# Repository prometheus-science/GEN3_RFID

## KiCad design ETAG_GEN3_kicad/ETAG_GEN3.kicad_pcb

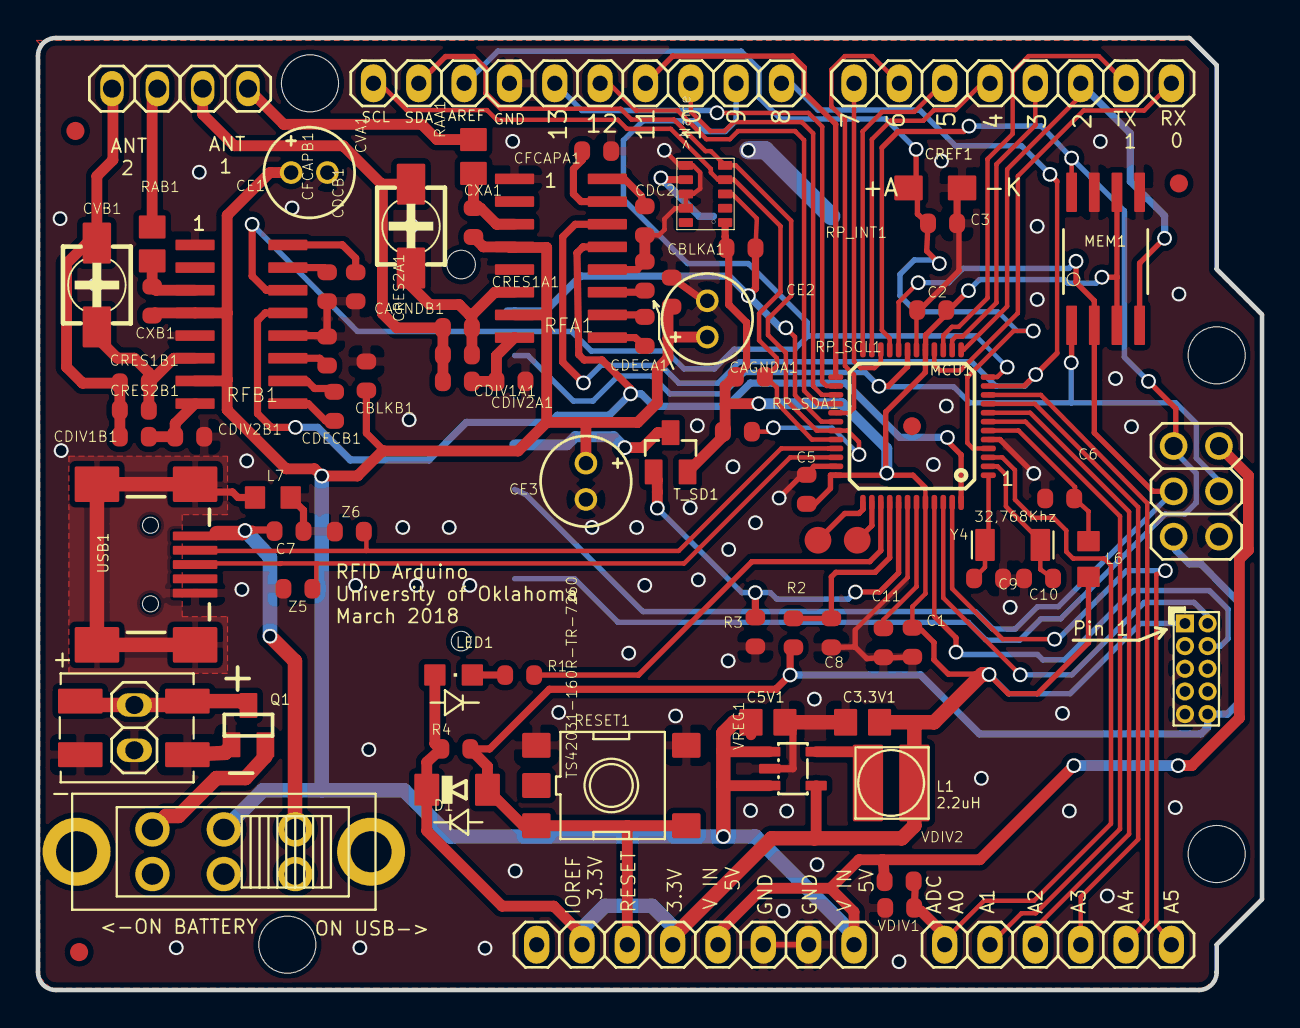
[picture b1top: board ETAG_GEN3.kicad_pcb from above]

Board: 2 copper layers, 68.6 x 53.3 mm, 89 parts (0 on the bottom side), 73 nets.

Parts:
@HOLE0, @HOLE1, @HOLE2, @HOLE3: (no value)
BAT1: 10MM_SM_COIN_CELL_CLIP
C1, C2, C3, C5, C6: 100nF; C0603-ROUND
C3.3V1, C5V1: 10uF; C0805
C7, C8: 10nF; C0603-ROUND
C9, C10: 22pF; C0603-ROUND
C11: 1uF; C0603-ROUND
CAGNDA1: 1uF; C0603-ROUND
CAGNDB1: 1uF; C0603-ROUND
CBLKA1: 100nF; C0603-ROUND
CBLKB1: 100nF; C0603-ROUND
CDC2: 10nF; C0603-ROUND
CDCB1: 10nF; C0603-ROUND
CDECA1: 100nF; C0603-ROUND
CDECB1: 100nF; C0603-ROUND
CDIV1A1, CDIV1B1: 22pF; C0603-ROUND
CDIV2A1, CDIV2B1: 1.5nF; C0603-ROUND
CE1, CE2, CE3: 150uF; E2-5
CFCAPA1: 10nF; C0603-ROUND
CFCAPB1: 10nF; C0603-ROUND
CON_P1: LITE_TRAP_2POS; LITE_TRAP_MINI
CREF1: 4.7uF; SMC_A
CRES1A1: 1.2nF; C0603-ROUND
CRES1B1: 1nF; C0603-ROUND
CRES2A1, CRES2B1: 100pF; C0603-ROUND
CVA1: 50pF; CTRIM3018_11
CVB1: 50pF; CTRIM3018_11
CXA1: 100nF; C0603-ROUND
CXB1: 100nF; C0603-ROUND
D1: CD1206-S01575; MINIMELF
FD1, FD2, FD3: FIDUCIALMOUNT; FIDUCIA-MOUNT
HDR_AD1: FH254-106DF08500V; 1X06
HDR_IOH1: FH254-110DF08500V; 1X10
HDR_IOL1: FH254-108DF08500V; 1X08
HDR_POWER1: FH254-108DF08500V; 1X08
ICSP6: 3x2M; 2X03
ICSP10: PINHEAD-2x5-P1.27; PINHEAD_2X05_127
JPA1: NA; 1X02
JPB1: NA; 1X02
JP_PWR1: NA; 1X02
L1: 2.2uH; SMT_COIL_INDUCTOR_4X4MM
L6, L7: MH2029-300Y; C0805K
LED1: Yellow; CHIPLED_0805
MCU1: SAMD21G18A-AUT; TQFP48-7X7
MEM1: AT45DB041BWIDE; SO08WIDE
Q1: FDN360P; SUPER-SOT3
R1: 100; C0603-ROUND
R2: 330; C0603-ROUND
R3: 10K; C0603-ROUND
R4: 10k; C0603-ROUND
RAA1: 22; C0805
RAB1: 22; R0805
RESET1: TS42031-160R-TR-7260; TS42
RFA1: EM4095; SO16
RFB1: EM4095; SO16
RP_INT1: 10k; C0603-ROUND
RP_SCL1: 10k; C0603-ROUND
RP_SDA1: 10k; C0603-ROUND
RTC1: MC-RTC-RV-1805-C3-I2C; MC-RTC-C3
SD1: SDMMC06132; 06132
SW1: MFS201N-9-Z
TP1, TP2: TPTP15R; TP15R
T_SD1: P_CHANNEL_MOSFET_; SOT23
USB1: USB-MINIB-5PIN; USB-MINIB
VDIV1: 500K; C0603-ROUND
VDIV2: 1.8M; C0603-ROUND
VREG1: LM3671; SOT23-5L
Y4: 32,768Khz; RESONATOR_EPSON_FC_145
Z5, Z6: ESD_SUPRESSOR; C0603-ROUND

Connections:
+3V3: C1.1, C2.2, C3.3V1.1, C5.1, D1.C, HDR_POWER1.2, HDR_POWER1.4, ICSP10.1, L1.P$2, L6.2, LED1.A, MCU1.17, MCU1.36, MCU1.44, MEM1.3, MEM1.6, R4.2, RP_INT1.2, RP_SCL1.2, RP_SDA1.2, RTC1.P$1, T_SD1.2, VREG1.4
/ETAG_GEN3_1/12_IN: CON_P1.P$3, CON_P1.P$4, JP_PWR1.2, Q1.3
/ETAG_GEN3_1/XUSB: C7.1, SW1.P$5, USB1.VBUS
/ETAG_GEN3_2/PA00_XIN32: C9.2, MCU1.1, Y4.P$1
/ETAG_GEN3_2/PA01_XOUT32: C10.2, MCU1.2, Y4.P$2
/ETAG_GEN3_2/PA03_AREFA: C3.1, CREF1.+, HDR_IOH1.8, MCU1.4
/ETAG_GEN3_2/PA04_AIN4: HDR_AD1.4, MCU1.9
/ETAG_GEN3_2/PA05_AIN5: HDR_AD1.5, MCU1.10
/ETAG_GEN3_2/PA09_TCC0-W1_PA9: HDR_IOL1.4, MCU1.14
/ETAG_GEN3_2/PA10_TCC0-W2_PA10: HDR_IOL1.2, MCU1.15
/ETAG_GEN3_2/PA11_TCC0-W3_PA11: HDR_IOL1.1, MCU1.16
/ETAG_GEN3_2/PA13: HDR_IOL1.8, MCU1.22
/ETAG_GEN3_2/PA14_TCC0-W4: HDR_IOL1.5, MCU1.23
/ETAG_GEN3_2/PA15_TCC0-W5: HDR_IOL1.6, MCU1.24
/ETAG_GEN3_2/PA16_MOSI: HDR_IOH1.4, MCU1.25
/ETAG_GEN3_2/PA17_SCK: HDR_IOH1.6, MCU1.26
/ETAG_GEN3_2/PA18_SS: HDR_IOH1.3, MCU1.27
/ETAG_GEN3_2/PA19_MISO: HDR_IOH1.5, MCU1.28
/ETAG_GEN3_2/PA20_TCC0-W6: HDR_IOL1.7, MCU1.29
/ETAG_GEN3_2/PA27_TX_LED: MCU1.39, R1.2
/ETAG_GEN3_2/PA30_SWCLK: ICSP10.4, MCU1.45
/ETAG_GEN3_2/PA31_SWDIO: ICSP10.2, MCU1.46
/ETAG_GEN3_2/PB02: HDR_AD1.6, MCU1.47
/ETAG_GEN3_2/PB08_AIN2: HDR_AD1.2, MCU1.7
/ETAG_GEN3_2/PB09_AIN3: HDR_AD1.3, MCU1.8
/ETAG_GEN3_2/PB22_DEBUG_TX: MCU1.37, TP2.TP
/ETAG_GEN3_2/PB23_DEBUG_RX: MCU1.38, TP1.TP
/ETAG_GEN3_2/RESET: D1.A, HDR_POWER1.3, ICSP6.5, ICSP10.10, R2.2, R4.1, RESET1.3, RESET1.4
/ETAG_GEN3_2/TARGET_RESET: C8.1, MCU1.40, R2.1
/ETAG_GEN3_2/VDDCORE: C11.1, MCU1.43
GND: BAT1.-, C1.2, C2.1, C3.2, C3.3V1.2, C5.2, C5V1.2, C6.2, C7.2, C8.2, C9.1, C10.1, C11.2, CAGNDA1.2, CAGNDB1.2, CBLKA1.2, CBLKB1.2, CDC2.2, CDCB1.2, CDIV2A1.2, CDIV2B1.2, CE1.-, CE2.-, CE3.-, CFCAPA1.2, CFCAPB1.2, CON_P1.P$1, CON_P1.P$2, CREF1.-, HDR_IOH1.7, HDR_POWER1.6, HDR_POWER1.7, ICSP6.6, ICSP10.3, ICSP10.5, ICSP10.9, JP_PWR1.1, L7.2, MCU1.5, MCU1.18, MCU1.35, MCU1.42, MEM1.5, MEM1.7, Q1.1, R3.2, RESET1.1, RESET1.2, RFA1.1, RFA1.5, RFA1.12, RFB1.1, RFB1.5, RFB1.12, RTC1.P$6, RTC1.P$8, RTC1.P$9, SD1.3, SD1.6, SD1.GP, SD1.GP3, USB1.GND, VDIV1.1, VREG1.2, Z5.1, Z6.1
unnamed: BAT1.+@1, BAT1.+@2, RTC1.P$7
unnamed: C6.1, L6.1, MCU1.6
unnamed: CAGNDA1.1, RFA1.11
unnamed: CAGNDB1.1, RFB1.11
unnamed: CDC2.1, RFA1.16
unnamed: CDCB1.1, RFB1.16
unnamed: CDECA1.1, RFA1.10
unnamed: CDECA1.2, RFA1.9
unnamed: CDECB1.1, RFB1.10
unnamed: CDECB1.2, RFB1.9
unnamed: CDIV1A1.1, CRES1A1.2, CRES2A1.2, CVA1.+, JPA1.1
unnamed: CDIV1A1.2, CDIV2A1.1, RFA1.8
unnamed: CDIV1B1.1, CRES1B1.2, CRES2B1.2, CVB1.+, JPB1.1
unnamed: CDIV1B1.2, CDIV2B1.1, RFB1.8
unnamed: CFCAPA1.1, RFA1.15
unnamed: CFCAPB1.1, RFB1.15
unnamed: CRES1A1.1, CRES2A1.1, CVA1.-, RFA1.6
unnamed: CRES1B1.1, CRES2B1.1, CVB1.-, RFB1.6
unnamed: CXA1.1, RAA1.2, RFA1.3
unnamed: CXB1.1, RAB1.2, RFB1.3
unnamed: JPA1.2, RAA1.1
unnamed: JPB1.2, RAB1.1
unnamed: L1.P$1, VREG1.5
unnamed: L7.1, USB1.MTN1, USB1.MTN2, USB1.MTN3, USB1.MTN4
unnamed: LED1.C, R1.1
unnamed: Q1.2, SW1.P$1
unnamed: SD1.4, T_SD1.3
PA02_AIN0: HDR_AD1.1, MCU1.3, VDIV1.2, VDIV2.1
PA6_RFID_SHD: HDR_IOH1.1, MCU1.11, RFA1.14
PA7_RFID_SHD2: HDR_IOH1.2, MCU1.12, RFB1.14
PA08_TCC0-W0_PA8: HDR_IOL1.3, MCU1.13, MEM1.4
PA21_INT&SDCS: MCU1.30, RP_INT1.1, RTC1.P$3, SD1.1
PA22_SDA: HDR_IOH1.9, MCU1.31, RP_SDA1.1, RTC1.P$5
PA23_SCL: HDR_IOH1.10, MCU1.32, RP_SCL1.1, RTC1.P$4
PA28_2FETS: MCU1.41, R3.1, T_SD1.1
PB03_RFIDIN: MCU1.48, RFA1.13, RFB1.13
PB10_S4_SPI_MOSI: ICSP6.4, MCU1.19, MEM1.1, SD1.2
PB11_S4_SPI_SCK: ICSP6.3, MCU1.20, MEM1.2, SD1.5
PB12_S4_SPI_MISO: ICSP6.1, MCU1.21, MEM1.8, SD1.7
TARGET_USB_N: MCU1.33, USB1.D-, Z6.2
TARGET_USB_P: MCU1.34, USB1.D+, Z5.2
V_IN: C5V1.1, CBLKA1.1, CBLKB1.1, CE1.+, CE2.+, CE3.+, CXA1.2, CXB1.2, HDR_POWER1.5, HDR_POWER1.8, ICSP6.2, RFA1.4, RFA1.7, RFB1.4, RFB1.7, SW1.P$3, VDIV2.2, VREG1.1, VREG1.3

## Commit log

2017-02-10 Mod3 traces complete
2017-02-17 Mod4 conceptual prototype
2017-02-20 Conceptual prototype 2 minor board edits
2017-03-06 Mod5 conceptual prototype with dual antenna and power supply
2017-03-08 Moved files around Added pin layout sheet
2017-03-08 Updated pin mapping list
2017-03-13 MArch13_PFETs added and pins rearranged
2017-03-15 Added 3.3V regulator for USB operation
2017-03-20 Jay's changes to voltage regulator
2017-04-05 dual level mosfet added to voltage divider
2017-04-11 Design submitted to PCB shop
2017-05-10 Design submitted to PCB shop update
2019-05-12 Removed old design files
2019-05-12 Updated files...
2021-04-26 cponvert board to kicad and prepare for kitspace
